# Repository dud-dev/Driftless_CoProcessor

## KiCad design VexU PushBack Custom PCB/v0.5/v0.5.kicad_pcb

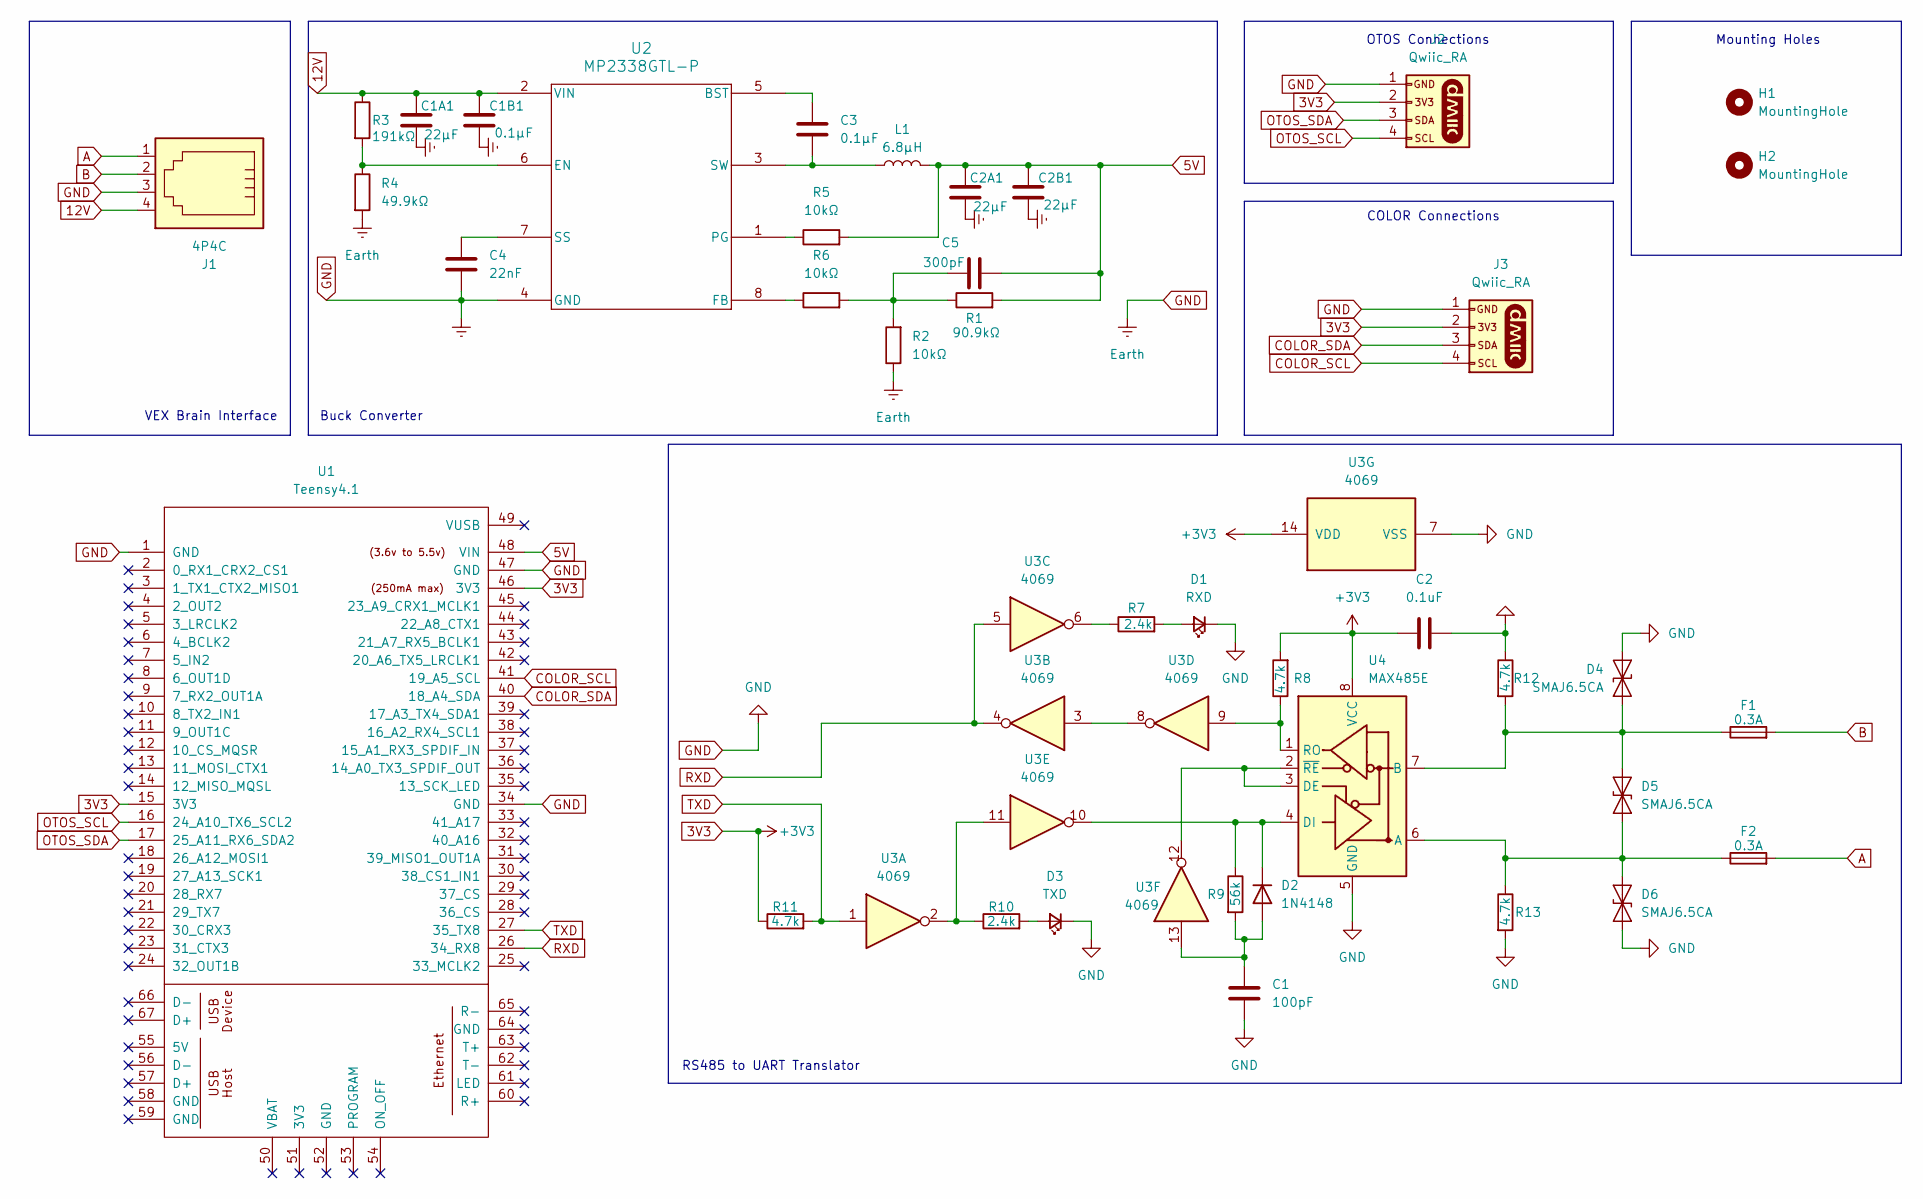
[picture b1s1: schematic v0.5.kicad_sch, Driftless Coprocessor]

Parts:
C1: 100pF; C_0402_1005Metric
C1A1, C2A1, C2B1: 22μF; C_1206_3216Metric
C1B1: 0.1μF; C_1206_3216Metric
C2: 0.1uF; C_0402_1005Metric
C3: 0.1μF; C_0402_1005Metric
C4: 22nF; C_0402_1005Metric
C5: 300pF; C_0402_1005Metric
D1: RXD; LED_0402_1005Metric
D2: 1N4148; D_DO-35_SOD27_P7.62mm_Horizontal
D3: TXD; LED_0402_1005Metric
D4, D5, D6: SMAJ6.5CA; D_SMA
F1, F2: 0.3A; Fuse_0603_1608Metric
H1, H2: MountingHole; MountingHole_3.2mm_M3
J1: 4P4C; RJ9_Evercom_5301-440xxx_Horizontal
J2, J3: Qwiic_RA; JST_1x04_P1.0mm_Horizontal_SMD
L1: 6.8μH; L_Coilcraft_XAL4030-XXX
R1: 90.9kΩ; R_0402_1005Metric
R2, R5, R6: 10kΩ; R_0402_1005Metric
R3: 191kΩ; R_0402_1005Metric
R4: 49.9kΩ; R_0402_1005Metric
R7, R10: 2.4k; R_0402_1005Metric
R8, R11, R12, R13: 4.7k; R_0402_1005Metric
R9: 56k; R_0402_1005Metric
U1: Teensy4.1; Teensy41
U2: MP2338GTL-P; SOT583_MP2338_MNP
U3: 4069; DIP-14_W7.62mm
U4: MAX485E; SOIC-8_3.9x4.9mm_P1.27mm

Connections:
3V3: C2.1, J2.2, J3.2, R8.2, R11.1, U1.15 (3V3), U1.46 (3V3), U3.14 (VDD), U4.8 (VCC)
5V: C2A1.1, C2B1.1, C5.2, L1.2, R1.2, R5.2, U1.48 (VIN)
12V: C1A1.1, C1B1.1, J1.4, R3.1, U2.2 (VIN)
A: F2.2, J1.1
B: F1.2, J1.2
COLOR_SCL: J3.4, U1.41 (19_A5_SCL)
COLOR_SDA: J3.3, U1.40 (18_A4_SDA)
GND: C1.2, C1A1.2, C1B1.2, C2.2, C2A1.2, C2B1.2, C4.2, D1.1 (K), D3.1 (K), D4.1 (A1), D6.1 (A1), J1.3, J2.1, J3.1, R2.1, R4.2, R12.1, R13.2, U1.1 (GND), U1.34 (GND), U1.47 (GND), U2.4 (GND), U3.7 (VSS), U4.5 (GND)
unnamed: C5.1, R1.1, R2.2, R6.2
unnamed: D1.2 (A), R7.2
unnamed: C1.1, D2.2 (A), R9.2, U3.13
unnamed: D2.1 (K), R9.1, U3.10, U4.4 (DI)
unnamed: D3.2 (A), R10.2
unnamed: D4.2 (A2), D5.2 (A2), F1.1, R12.2, U4.7 (B)
unnamed: D5.1 (A1), D6.2 (A2), F2.1, R13.1, U4.6 (A)
unnamed: R7.1, U3.6
unnamed: R10.1, U3.2, U3.11
unnamed: C3.1, U2.5 (BST)
unnamed: R3.2, R4.1, U2.6 (EN)
unnamed: R6.1, U2.8 (FB)
unnamed: R5.1, U2.1 (PG)
unnamed: C4.1, U2.7 (SS)
unnamed: C3.2, L1.1, U2.3 (SW)
unnamed: U3.3, U3.8
unnamed: U3.12, U4.2 (~RE), U4.3 (DE)
unnamed: R8.1, U3.9, U4.1 (RO)
OTOS_SCL: J2.4, U1.16 (24_A10_TX6_SCL2)
OTOS_SDA: J2.3, U1.17 (25_A11_RX6_SDA2)
RXD: U1.26 (34_RX8), U3.4, U3.5
TXD: R11.2, U1.27 (35_TX8), U3.1

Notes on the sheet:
Buck Converter
COLOR Connections
Mounting Holes
VEX Brain Interface
RS485 to UART Translator
OTOS Connections

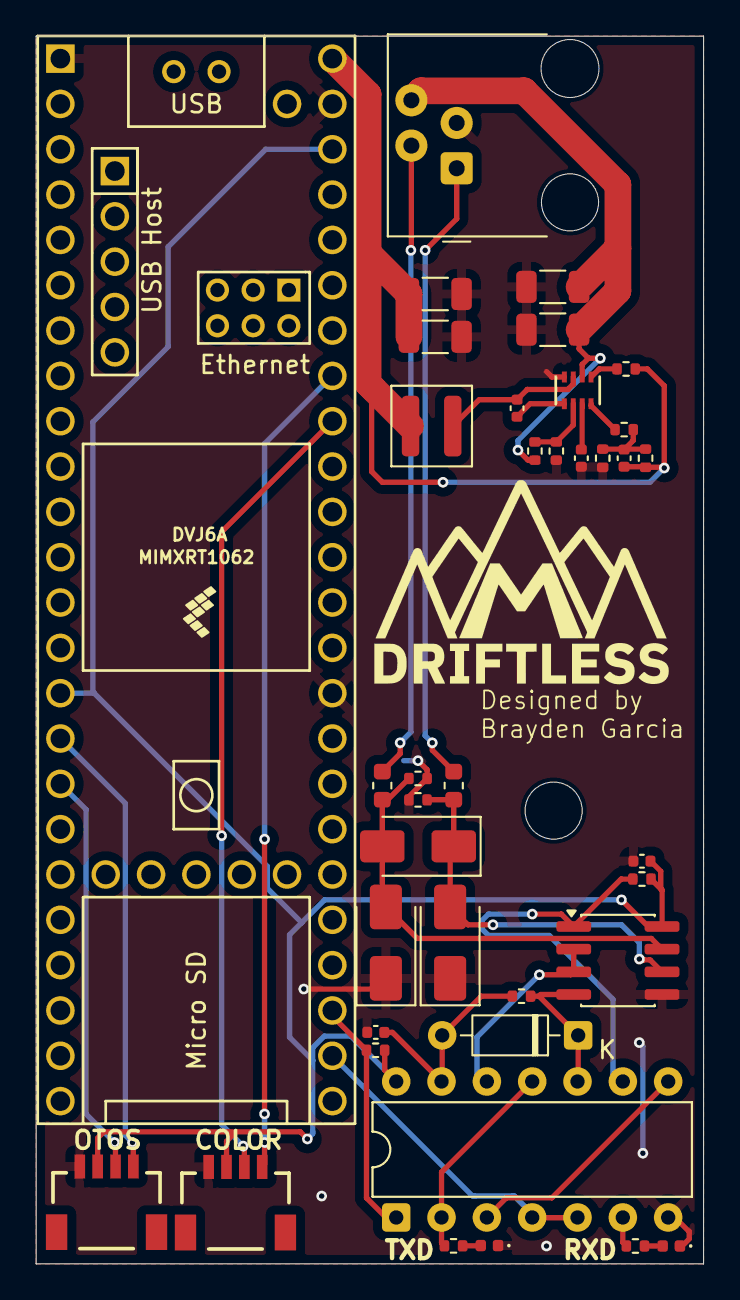
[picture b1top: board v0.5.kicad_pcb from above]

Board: 2 copper layers, 37.4 x 68.8 mm, 39 parts (0 on the bottom side), 30 nets.

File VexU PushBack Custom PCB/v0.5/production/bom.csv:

Designator,Footprint,Quantity,Value,LCSC Part #
C1,0402,1,100pF,
"C1A1, C2A1, C2B1",1206,3,22μF,
C1B1,1206,1,0.1μF,
C2,0402,1,0.1uF,
C3,0402,1,0.1μF,
C4,0402,1,22nF,
C5,0402,1,300pF,
D1,0402,1,RXD,
D2,D_DO-35_SOD27_P7.62mm_Horizontal,1,1N4148,
D3,0402,1,TXD,
"D4, D5, D6",D_SMA,3,SMAJ6.5CA,
"F1, F2",0603,2,0.3A,
J1,RJ9_Evercom_5301-440xxx_Horizontal,1,4P4C,
"J2, J3",JST_1x04_P1.0mm_Horizontal_SMD,2,Qwiic_RA,
L1,L_Coilcraft_XAL4030-XXX,1,6.8μH,
R1,0402,1,90.9kΩ,
"R10, R7",0402,2,2.4k,
"R11, R12, R13, R8",0402,4,4.7k,
"R2, R5, R6",0402,3,10kΩ,
R3,0402,1,191kΩ,
R4,0402,1,49.9kΩ,
R9,0402,1,56k,
U1,Teensy41,1,Teensy4.1,
U2,SOT583_MP2338_MNP,1,MP2338GTL-P,
U3,DIP-14_W7.62mm,1,4069,
U4,SOIC-8_3.9x4.9mm_P1.27mm,1,MAX485E,

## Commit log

2026-02-24 Working Version 0.5
    The prototype is currently operational with the buck converter performing as expected (5.04V output). Please note that the RXD and TXD pins are swapped in the current schematic. We are utilizing a so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
2026-03-01 Schematic fully done
    will need to keep working on tracing and component layout
2026-03-02 Layout of buck convertr
2026-03-02 Different Partial Layout Design
    Still have to do tracing and finishing layout
2026-03-02 Layout redesign for tigher component placing
    Changed switch sized and mad layout smaler
2026-03-08 Added SparkFun Library
    Switched 1mm 1x4 connect out for QWIIC connector
2026-03-08 Imported SparkFun Library
    Imported SparkFun library into main file to branch off into different test cases
2026-03-08 Updating Footprints & Symbols
    Updating Main branch with updated footprints & symbols before branching
2026-03-09 Finishied Schematic
    Start work on 4 layer board tracing
2026-03-24 Finished Routing PCB
    Pushed For production
2026-06-01 Worlds Push
    Season Over
